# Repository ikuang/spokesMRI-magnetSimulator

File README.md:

# spokesMRI-magnetSimulator
 
 Matlab simulator for magnetic fields generated by 'spokes-and-hub' permanent magnet arrays as presented at ISMRM 2019 [1].
 
 To input magnet geometries and run simulator use:
 ```matlab 
 testMagnet.m
 ```
 
 We have provided [STL](stl) files for a 191 mT magnet constructed using 64 bar magnets (1/2" x 1/8" x 1") from [K&J Magnets](https://www.kjmagnetics.com/proddetail.asp?prod=B82X0).

 We use mechanical tilts from linear actuators to generate gradient fields within the magnet [2]. The actuators and their control boards were purchased from [Actuonix](https://www.actuonix.com/L12-P-Micro-Linear-Actuator-with-Position-Feedback-p/l12-p.htm). Instructions and [DXF](dxf) files for laser cutting acrylic are provided as well.

 We use an 8-channel STHV800 ultrasound h-bridge driver chip from [STMicroelectronics](https://www.st.com/en/switches-and-multiplexers/sthv800.html) to transmit/receive RF on a solenoid coil [3]. A Teensy 4.0 microcontroller sends RF pulses to the driver. We have provided a sample dithered RF pulse (centered at 8.18MHz with 100kHz bandwidth), Arduino code that controls the pulses and actuator movements, and Eagle PCB layouts for the ultrasound chip board. These files are found in the [signalChain](./signalChain) directory. We use a USB oscilloscope from Pico Technology ([PicoScope 5243D](https://www.picotech.com/oscilloscope/5000/flexible-resolution-oscilloscope)) to capture MR data at the Larmor frequency and perform filtering and downsampling in software. Pico Technology provides open source software development kits for Python and Matlab implementations (https://github.com/picotech). 

## References

[1] Kuang, I., Arango, N., Stockmann, J., Adalsteinsson, E., White, J. <em>Equivalent-Charge-Based Optimization of Spokes-and-Hub Magnets for Hand-Held and Classroom MR Imaging</em>. Proc. Intl. Soc. Mag. Reson. Med., 2019. 

[2] Kuang, I., Stockmann, J., Adalsteinsson, E., White, J. <em>Mechanical Tilt-Induced Gradient Fields for Low-Field Spokes-and-Hub MR Imagers</em>. Proc. Intl. Soc. Mag. Reson. Med., 2021. 

[3] Kuang, I., Arango, N., Stockmann, J., Adalsteinsson, E., White, J. <em>Bloch-Optimized Dithered-Ultrasound-Pulse RF for Low-Field Inhomogeneous Permanent Magnet MR Imagers</em>. Proc. Intl. Soc. Mag. Reson. Med., 2020. 
 
 Plotting functions use perceptually uniform colormaps from https://colorcet.com/

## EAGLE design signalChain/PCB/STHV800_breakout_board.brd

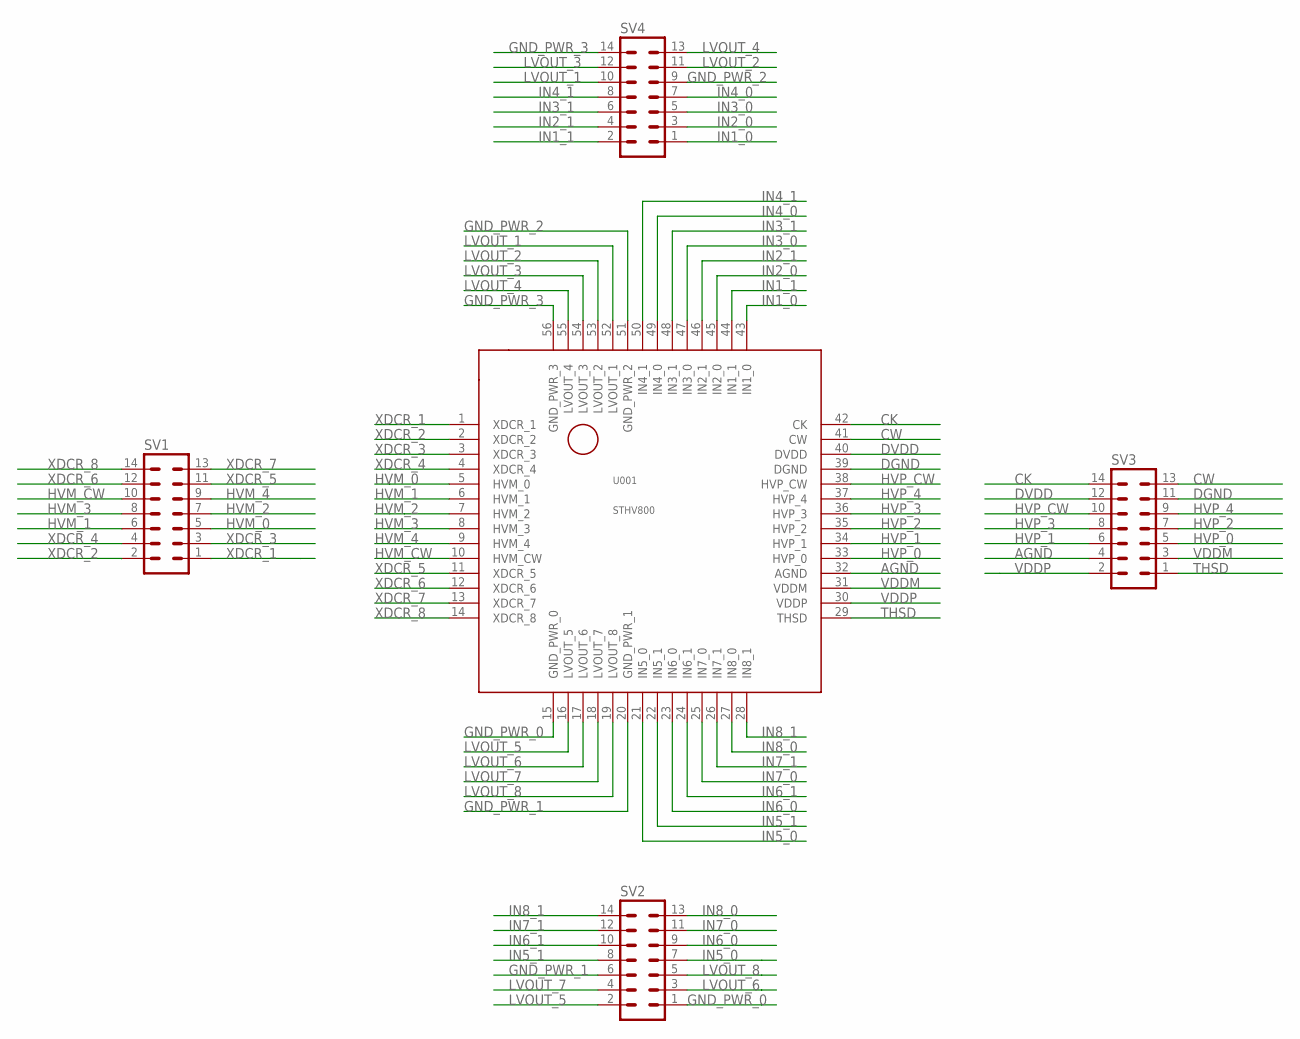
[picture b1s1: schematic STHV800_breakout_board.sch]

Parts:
SV1, SV2, SV3, SV4: MA07-2
U001: STHV800

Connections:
AGND: SV3.4, U001.32 (AGND)
CK: SV3.14, U001.42 (CK)
CW: SV3.13, U001.41 (CW)
DGND: SV3.11, U001.39 (DGND)
DVDD: SV3.12, U001.40 (DVDD)
GND_PWR_0: SV2.1, U001.15 (GND_PWR_0)
GND_PWR_1: SV2.6, U001.20 (GND_PWR_1)
GND_PWR_2: SV4.9, U001.51 (GND_PWR_2)
GND_PWR_3: SV4.14, U001.56 (GND_PWR_3)
HVM_0: SV1.5, U001.5 (HVM_0)
HVM_1: SV1.6, U001.6 (HVM_1)
HVM_2: SV1.7, U001.7 (HVM_2)
HVM_3: SV1.8, U001.8 (HVM_3)
HVM_4: SV1.9, U001.9 (HVM_4)
HVM_CW: SV1.10, U001.10 (HVM_CW)
HVP_0: SV3.5, U001.33 (HVP_0)
HVP_1: SV3.6, U001.34 (HVP_1)
HVP_2: SV3.7, U001.35 (HVP_2)
HVP_3: SV3.8, U001.36 (HVP_3)
HVP_4: SV3.9, U001.37 (HVP_4)
HVP_CW: SV3.10, U001.38 (HVP_CW)
IN1_0: SV4.1, U001.43 (IN1_0)
IN1_1: SV4.2, U001.44 (IN1_1)
IN2_0: SV4.3, U001.45 (IN2_0)
IN2_1: SV4.4, U001.46 (IN2_1)
IN3_0: SV4.5, U001.47 (IN3_0)
IN3_1: SV4.6, U001.48 (IN3_1)
IN4_0: SV4.7, U001.49 (IN4_0)
IN4_1: SV4.8, U001.50 (IN4_1)
IN5_0: SV2.7, U001.21 (IN5_0)
IN5_1: SV2.8, U001.22 (IN5_1)
IN6_0: SV2.9, U001.23 (IN6_0)
IN6_1: SV2.10, U001.24 (IN6_1)
IN7_0: SV2.11, U001.25 (IN7_0)
IN7_1: SV2.12, U001.26 (IN7_1)
IN8_0: SV2.13, U001.27 (IN8_0)
IN8_1: SV2.14, U001.28 (IN8_1)
LVOUT_1: SV4.10, U001.52 (LVOUT_1)
LVOUT_2: SV4.11, U001.53 (LVOUT_2)
LVOUT_3: SV4.12, U001.54 (LVOUT_3)
LVOUT_4: SV4.13, U001.55 (LVOUT_4)
LVOUT_5: SV2.2, U001.16 (LVOUT_5)
LVOUT_6: SV2.3, U001.17 (LVOUT_6)
LVOUT_7: SV2.4, U001.18 (LVOUT_7)
LVOUT_8: SV2.5, U001.19 (LVOUT_8)
THSD: SV3.1, U001.29 (THSD)
VDDM: SV3.3, U001.31 (VDDM)
VDDP: SV3.2, U001.30 (VDDP)
XDCR_1: SV1.1, U001.1 (XDCR_1)
XDCR_2: SV1.2, U001.2 (XDCR_2)
XDCR_3: SV1.3, U001.3 (XDCR_3)
XDCR_4: SV1.4, U001.4 (XDCR_4)
XDCR_5: SV1.11, U001.11 (XDCR_5)
XDCR_6: SV1.12, U001.12 (XDCR_6)
XDCR_7: SV1.13, U001.13 (XDCR_7)
XDCR_8: SV1.14, U001.14 (XDCR_8)

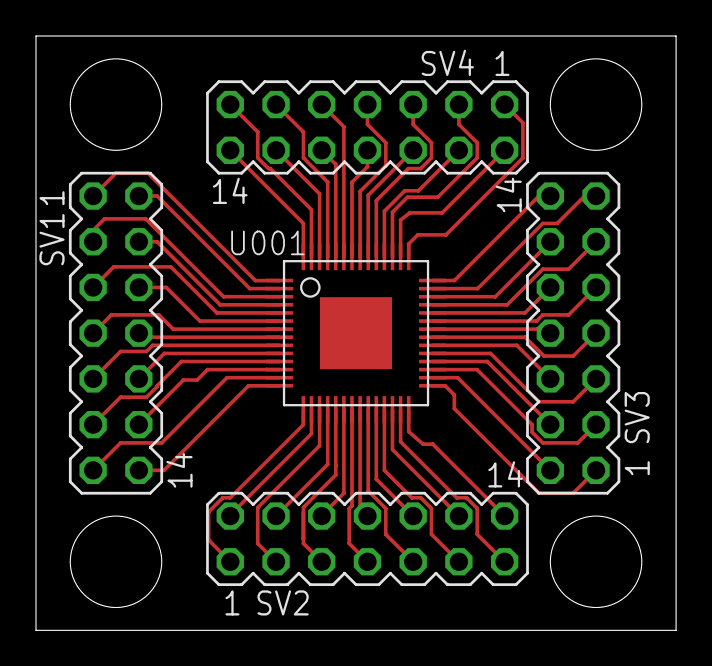
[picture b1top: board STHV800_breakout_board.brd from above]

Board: 2 copper layers, 35.6 x 33.0 mm, 5 parts (0 on the bottom side), 56 nets.

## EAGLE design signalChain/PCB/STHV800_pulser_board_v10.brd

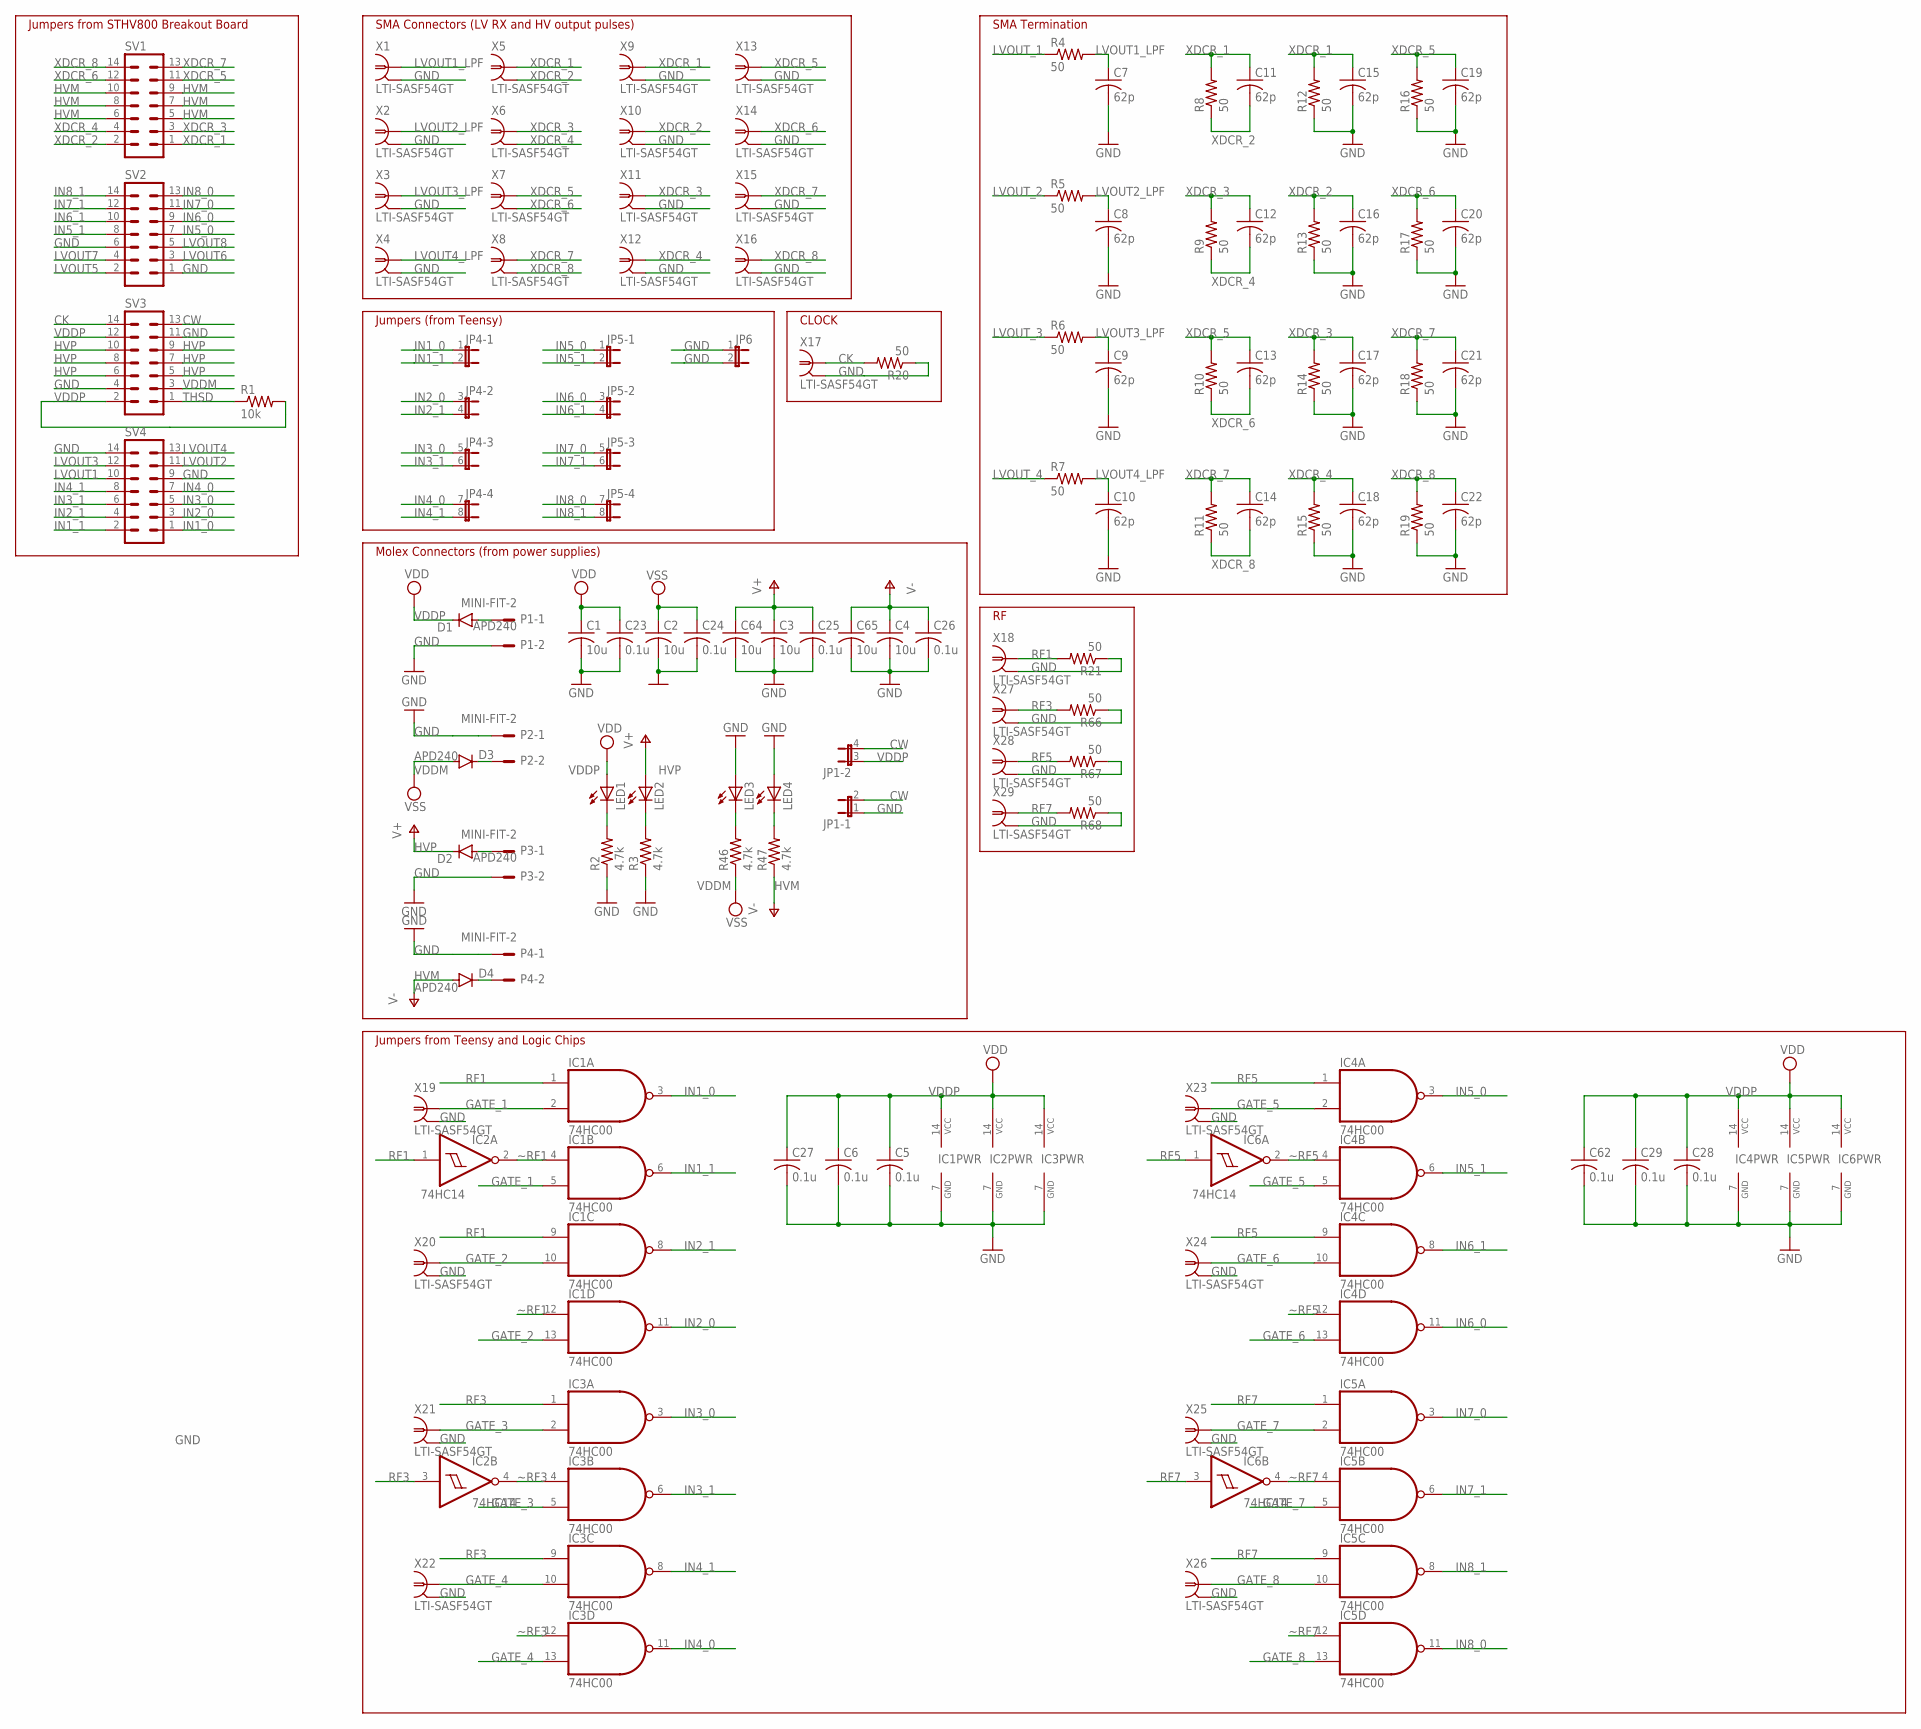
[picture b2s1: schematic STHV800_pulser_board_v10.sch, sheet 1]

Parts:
C1, C2: 10u; C1206
C3, C4, C64, C65: 10u; C1210
C5, C6, C23, C24, C25, C26, C27, C28, C29, C62: 0.1u; C0805
C7, C8, C9, C10, C11, C12, C13, C14, C15, C16, C17, C18, C19, C20, C21, C22: 62p; C0805
D1, D2, D3, D4: APD240; SOD-123_MINI-SMA
IC1, IC3, IC4, IC5: 74HC00; TSSOP14
IC2, IC6: 74HC14; TSSOP14
JP1: JP2QE; JP2Q
JP4, JP5: JP4QE; JP4Q
JP6: JP1E; JP1
LED1, LED2, LED3, LED4: LEDSMT1206; 1206
P1, P2, P3, P4: MINI-FIT-2; CON-MOLEX-MINI-FIT_39-30-?02?
R1: 10k; R0805
R2, R3, R46, R47: 4.7k; R0805
R4, R5, R6, R7, R8, R9, R10, R11, R12, R13, R14, R15, R16, R17, R18, R19: 50; R1206
R20, R21, R66, R67, R68: 50; R0805
SV1, SV2, SV3, SV4: MA07-2
X1, X2, X3, X4, X5, X6, X7, X8, X9, X10, X11, X12, X13, X14, X15, X16, X17, X18, X19, X20, X21, X22, X23, X24, X25, X26, X27, X28, X29: LTI-SASF54GT

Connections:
CK: R20.2, SV3.14, X17.1
CW: JP1.2, JP1.4 (2), SV3.13
GATE_1: IC1.2 (I1), IC1.5 (I1), X19.1
GATE_2: IC1.10 (I1), IC1.13 (I1), X20.1
GATE_3: IC3.2 (I1), IC3.5 (I1), X21.1
GATE_4: IC3.10 (I1), IC3.13 (I1), X22.1
GATE_5: IC4.2 (I1), IC4.5 (I1), X23.1
GATE_6: IC4.10 (I1), IC4.13 (I1), X24.1
GATE_7: IC5.2 (I1), IC5.5 (I1), X25.1
GATE_8: IC5.10 (I1), IC5.13 (I1), X26.1
GND: C1.2, C2.2, C3.2, C4.2, C5.2, C6.2, C7.2, C8.2, C9.2, C10.2, C15.2, C16.2, C17.2, C18.2, C19.2, C20.2, C21.2, C22.2, C23.2, C24.2, C25.2, C26.2, C27.2, C28.2, C29.2, C62.2, C64.2, C65.2, IC1.7 (GND), IC2.7 (GND), IC3.7 (GND), IC4.7 (GND), IC5.7 (GND), IC6.7 (GND), JP1.1, JP6.1, JP6.2, LED3.A, LED4.A, P1.2, P2.1, P3.2, P4.1, R2.1, R3.1, R12.1, R13.1, R14.1, R15.1, R16.1, R17.1, R18.1, R19.1, R20.1, R21.1, R66.1, R67.1, R68.1, SV2.1, SV2.6, SV3.4, SV3.11, SV4.9, SV4.14, X1.2, X1.3 (2), X1.4 (2), X1.5 (2), X2.2, X2.3 (2), X2.4 (2), X2.5 (2), X3.2, X3.3 (2), X3.4 (2), X3.5 (2), X4.2, X4.3 (2), X4.4 (2), X4.5 (2), X9.2, X9.3 (2), X9.4 (2), X9.5 (2), X10.2, X10.3 (2), X10.4 (2), X10.5 (2), X11.2, X11.3 (2), X11.4 (2), X11.5 (2), X12.2, X12.3 (2), X12.4 (2), X12.5 (2), X13.2, X13.3 (2), X13.4 (2), X13.5 (2), X14.2, X14.3 (2), X14.4 (2), X14.5 (2), X15.2, X15.3 (2), X15.4 (2), X15.5 (2), X16.2, X16.3 (2), X16.4 (2), X16.5 (2), X17.2, X17.3 (2), X17.4 (2), X17.5 (2), X18.2, X18.3 (2), X18.4 (2), X18.5 (2), X19.2, X19.3 (2), X19.4 (2), X19.5 (2), X20.2, X20.3 (2), X20.4 (2), X20.5 (2), X21.2, X21.3 (2), X21.4 (2), X21.5 (2), X22.2, X22.3 (2), X22.4 (2), X22.5 (2), X23.2, X23.3 (2), X23.4 (2), X23.5 (2), X24.2, X24.3 (2), X24.4 (2), X24.5 (2), X25.2, X25.3 (2), X25.4 (2), X25.5 (2), X26.2, X26.3 (2), X26.4 (2), X26.5 (2), X27.2, X27.3 (2), X27.4 (2), X27.5 (2), X28.2, X28.3 (2), X28.4 (2), X28.5 (2), X29.2, X29.3 (2), X29.4 (2), X29.5 (2); also elsewhere on the board
HVM: C4.1, C26.1, C65.1, D4.A, R47.1, SV1.5, SV1.6, SV1.7, SV1.8, SV1.9, SV1.10
HVP: C3.1, C25.1, C64.1, D2.C, LED2.A, SV3.5, SV3.6, SV3.7, SV3.8, SV3.9, SV3.10
HVP_1: D2.A, P3.1
IN1_0: IC1.3 (O), JP4.1, SV4.1
IN1_1: IC1.6 (O), JP4.2, SV4.2
IN2_0: IC1.11 (O), JP4.3 (1), SV4.3
IN2_1: IC1.8 (O), JP4.4 (2), SV4.4
IN3_0: IC3.3 (O), JP4.5 (1), SV4.5
IN3_1: IC3.6 (O), JP4.6 (2), SV4.6
IN4_0: IC3.11 (O), JP4.7 (1), SV4.7
IN4_1: IC3.8 (O), JP4.8 (2), SV4.8
IN5_0: IC4.3 (O), JP5.1, SV2.7
IN5_1: IC4.6 (O), JP5.2, SV2.8
IN6_0: IC4.11 (O), JP5.3 (1), SV2.9
IN6_1: IC4.8 (O), JP5.4 (2), SV2.10
IN7_0: IC5.3 (O), JP5.5 (1), SV2.11
IN7_1: IC5.6 (O), JP5.6 (2), SV2.12
IN8_0: IC5.11 (O), JP5.7 (1), SV2.13
IN8_1: IC5.8 (O), JP5.8 (2), SV2.14
LVOUT1: SV4.10; also elsewhere on the board
LVOUT1_LPF: C7.1, R4.2, X1.1
LVOUT2: SV4.11; also elsewhere on the board
LVOUT2_LPF: C8.1, R5.2, X2.1
LVOUT3: SV4.12; also elsewhere on the board
LVOUT3_LPF: C9.1, R6.2, X3.1
LVOUT4: SV4.13; also elsewhere on the board
LVOUT4_LPF: C10.1, R7.2, X4.1
LVOUT5: SV2.2; also elsewhere on the board
LVOUT6: SV2.3; also elsewhere on the board
LVOUT7: SV2.4; also elsewhere on the board
LVOUT8: SV2.5; also elsewhere on the board
LVOUT_1: R4.1; also elsewhere on the board
LVOUT_2: R5.1; also elsewhere on the board
LVOUT_3: R6.1; also elsewhere on the board
LVOUT_4: R7.1; also elsewhere on the board
unnamed: LED1.C, R2.2
unnamed: LED2.C, R3.2
unnamed: LED3.C, R46.2
unnamed: LED4.C, R47.2
unnamed: D3.C, P2.2
unnamed: D4.C, P4.2
RF1: IC1.1 (I0), IC1.9 (I0), IC2.1 (I), R21.2, X18.1
RF3: IC2.3 (I), IC3.1 (I0), IC3.9 (I0), R66.2, X27.1
RF5: IC4.1 (I0), IC4.9 (I0), IC6.1 (I), R67.2, X28.1
RF7: IC5.1 (I0), IC5.9 (I0), IC6.3 (I), R68.2, X29.1
THSD: R1.1, SV3.1
VDDM: C2.1, C24.1, D3.A, R46.1, SV3.3; also elsewhere on the board
VDDP: C1.1, C5.1, C6.1, C23.1, C27.1, C28.1, C29.1, C62.1, D1.C, IC1.14 (VCC), IC2.14 (VCC), IC3.14 (VCC), IC4.14 (VCC), IC5.14 (VCC), IC6.14 (VCC), JP1.3 (1), LED1.A, R1.2, SV3.2, SV3.12; also elsewhere on the board
VDDP_1: D1.A, P1.1
XDCR_1: C11.1, C15.1, R8.2, R12.2, SV1.1, X5.1, X9.1
XDCR_2: C11.2, C16.1, R8.1, R13.2, SV1.2, X5.2, X5.3 (2), X5.4 (2), X5.5 (2), X10.1
XDCR_3: C12.1, C17.1, R9.2, R14.2, SV1.3, X6.1, X11.1
XDCR_4: C12.2, C18.1, R9.1, R15.2, SV1.4, X6.2, X6.3 (2), X6.4 (2), X6.5 (2), X12.1
XDCR_5: C13.1, C19.1, R10.2, R16.2, SV1.11, X7.1, X13.1
XDCR_6: C13.2, C20.1, R10.1, R17.2, SV1.12, X7.2, X7.3 (2), X7.4 (2), X7.5 (2), X14.1
XDCR_7: C14.1, C21.1, R11.2, R18.2, SV1.13, X8.1, X15.1
XDCR_8: C14.2, C22.1, R11.1, R19.2, SV1.14, X8.2, X8.3 (2), X8.4 (2), X8.5 (2), X16.1
~RF1: IC1.4 (I0), IC1.12 (I0), IC2.2 (O)
~RF3: IC2.4 (O), IC3.4 (I0), IC3.12 (I0)
~RF5: IC4.4 (I0), IC4.12 (I0), IC6.2 (O)
~RF7: IC5.4 (I0), IC5.12 (I0), IC6.4 (O)

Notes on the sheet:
SMA Connectors (LV RX and HV output pulses)
Jumpers (from Teensy)
Molex Connectors (from power supplies)
CLOCK
Jumpers from Teensy and Logic Chips
Jumpers from STHV800 Breakout Board
SMA Termination

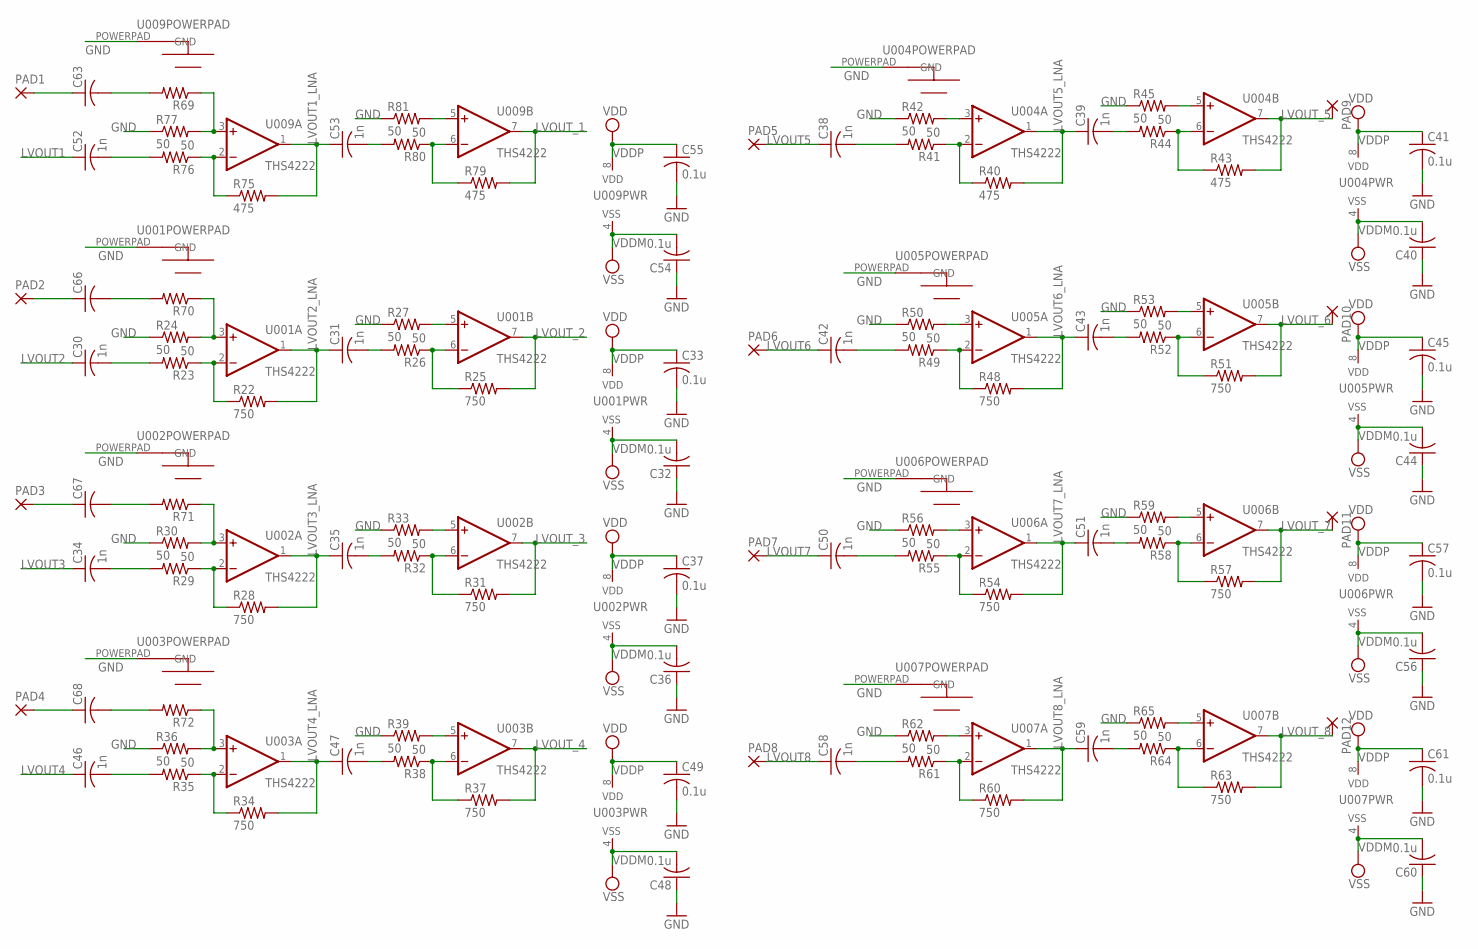
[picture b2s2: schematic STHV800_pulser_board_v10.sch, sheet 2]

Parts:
C30, C31, C34, C35, C38, C39, C42, C43, C46, C47, C50, C51, C52, C53, C58, C59: 1n; C0805
C32, C33, C36, C37, C40, C41, C44, C45, C48, C49, C54, C55, C56, C57, C60, C61: 0.1u; C0805
C63, C66, C67, C68: C-USC0805; C0805
PAD1, PAD2, PAD3, PAD4, PAD5, PAD6, PAD7, PAD8, PAD9, PAD10, PAD11, PAD12: 1,6/0,8
R22, R25, R28, R31, R34, R37, R48, R51, R54, R57, R60, R63: 750; R0805
R23, R24, R26, R27, R29, R30, R32, R33, R35, R36, R38, R39, R41, R42, R44, R45, R49, R50, R52, R53, R55, R56, R58, R59, R61, R62, R64, R65, R76, R77, R80, R81: 50; R0805
R40, R43, R75, R79: 475; R0805
R69, R70, R71, R72: R-US_R0805; R0805
U001, U002, U003, U004, U005, U006, U007, U009: THS4222; SSOP08-POWERPAD

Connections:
GND: C32.1, C33.2, C36.1, C37.2, C40.1, C41.2, C44.1, C45.2, C48.1, C49.2, C54.1, C55.2, C56.1, C57.2, C60.1, C61.2, R24.1, R27.1, R30.1, R33.1, R36.1, R39.1, R42.1, R45.1, R50.1, R53.1, R56.1, R59.1, R62.1, R65.1, R77.1, R81.1, U001.POWERPAD (GND), U002.POWERPAD (GND), U003.POWERPAD (GND), U004.POWERPAD (GND), U005.POWERPAD (GND), U006.POWERPAD (GND), U007.POWERPAD (GND), U009.POWERPAD (GND); also elsewhere on the board
LVOUT1: C52.1; also elsewhere on the board
LVOUT1_LNA: C53.1, R75.2, U009.1 (OUT)
LVOUT2: C30.1; also elsewhere on the board
LVOUT2_LNA: C31.1, R22.2, U001.1 (OUT)
LVOUT3: C34.1; also elsewhere on the board
LVOUT3_LNA: C35.1, R28.2, U002.1 (OUT)
LVOUT4: C46.1; also elsewhere on the board
LVOUT4_LNA: C47.1, R34.2, U003.1 (OUT)
LVOUT5: C38.1, PAD5.1; also elsewhere on the board
LVOUT5_LNA: C39.1, R40.2, U004.1 (OUT)
LVOUT6: C42.1, PAD6.1; also elsewhere on the board
LVOUT6_LNA: C43.1, R48.2, U005.1 (OUT)
LVOUT7: C50.1, PAD7.1; also elsewhere on the board
LVOUT7_LNA: C51.1, R54.2, U006.1 (OUT)
LVOUT8: C58.1, PAD8.1; also elsewhere on the board
LVOUT8_LNA: C59.1, R60.2, U007.1 (OUT)
LVOUT_1: R79.2, U009.7 (OUT); also elsewhere on the board
LVOUT_2: R25.2, U001.7 (OUT); also elsewhere on the board
LVOUT_3: R31.2, U002.7 (OUT); also elsewhere on the board
LVOUT_4: R37.2, U003.7 (OUT); also elsewhere on the board
LVOUT_5: PAD9.1, R43.2, U004.7 (OUT)
LVOUT_6: PAD10.1, R51.2, U005.7 (OUT)
LVOUT_7: PAD11.1, R57.2, U006.7 (OUT)
LVOUT_8: PAD12.1, R63.2, U007.7 (OUT)
unnamed: R25.1, R26.1, U001.6 (-IN)
unnamed: R24.2, R70.1, U001.3 (+IN)
unnamed: R22.1, R23.1, U001.2 (-IN)
unnamed: C30.2, R23.2
unnamed: C31.2, R26.2
unnamed: R27.2, U001.5 (+IN)
unnamed: R31.1, R32.1, U002.6 (-IN)
unnamed: R30.2, R71.1, U002.3 (+IN)
unnamed: R43.1, R44.1, U004.6 (-IN)
unnamed: R42.2, U004.3 (+IN)
unnamed: R40.1, R41.1, U004.2 (-IN)
unnamed: C38.2, R41.2
unnamed: C39.2, R44.2
unnamed: R45.2, U004.5 (+IN)
unnamed: R51.1, R52.1, U005.6 (-IN)
unnamed: R28.1, R29.1, U002.2 (-IN)
unnamed: C34.2, R29.2
unnamed: C35.2, R32.2
unnamed: R33.2, U002.5 (+IN)
unnamed: R37.1, R38.1, U003.6 (-IN)
unnamed: R36.2, R72.1, U003.3 (+IN)
unnamed: R34.1, R35.1, U003.2 (-IN)
unnamed: C46.2, R35.2
unnamed: C47.2, R38.2
unnamed: R39.2, U003.5 (+IN)
unnamed: R50.2, U005.3 (+IN)
unnamed: R48.1, R49.1, U005.2 (-IN)
unnamed: C42.2, R49.2
unnamed: C43.2, R52.2
unnamed: R53.2, U005.5 (+IN)
unnamed: R57.1, R58.1, U006.6 (-IN)
unnamed: R56.2, U006.3 (+IN)
unnamed: R54.1, R55.1, U006.2 (-IN)
unnamed: C50.2, R55.2
unnamed: C51.2, R58.2
unnamed: R59.2, U006.5 (+IN)
unnamed: R63.1, R64.1, U007.6 (-IN)
unnamed: R62.2, U007.3 (+IN)
unnamed: R60.1, R61.1, U007.2 (-IN)
unnamed: C58.2, R61.2
unnamed: C59.2, R64.2
unnamed: R65.2, U007.5 (+IN)
unnamed: C63.2, R69.2
unnamed: C67.2, R71.2
unnamed: C66.2, R70.2
unnamed: C68.2, R72.2
unnamed: R79.1, R80.1, U009.6 (-IN)
unnamed: R69.1, R77.2, U009.3 (+IN)
unnamed: R75.1, R76.1, U009.2 (-IN)
unnamed: C52.2, R76.2
unnamed: C53.2, R80.2
unnamed: R81.2, U009.5 (+IN)
TEST_VIA_1: C63.1, PAD1.1
TEST_VIA_2: C66.1, PAD2.1
TEST_VIA_3: C67.1, PAD3.1
TEST_VIA_4: C68.1, PAD4.1
VDDM: C32.2, C36.2, C40.2, C44.2, C48.2, C54.2, C56.2, C60.2, U001.4 (VSS), U002.4 (VSS), U003.4 (VSS), U004.4 (VSS), U005.4 (VSS), U006.4 (VSS), U007.4 (VSS), U009.4 (VSS); also elsewhere on the board
VDDP: C33.1, C37.1, C41.1, C45.1, C49.1, C55.1, C57.1, C61.1, U001.8 (VDD), U002.8 (VDD), U003.8 (VDD), U004.8 (VDD), U005.8 (VDD), U006.8 (VDD), U007.8 (VDD), U009.8 (VDD); also elsewhere on the board

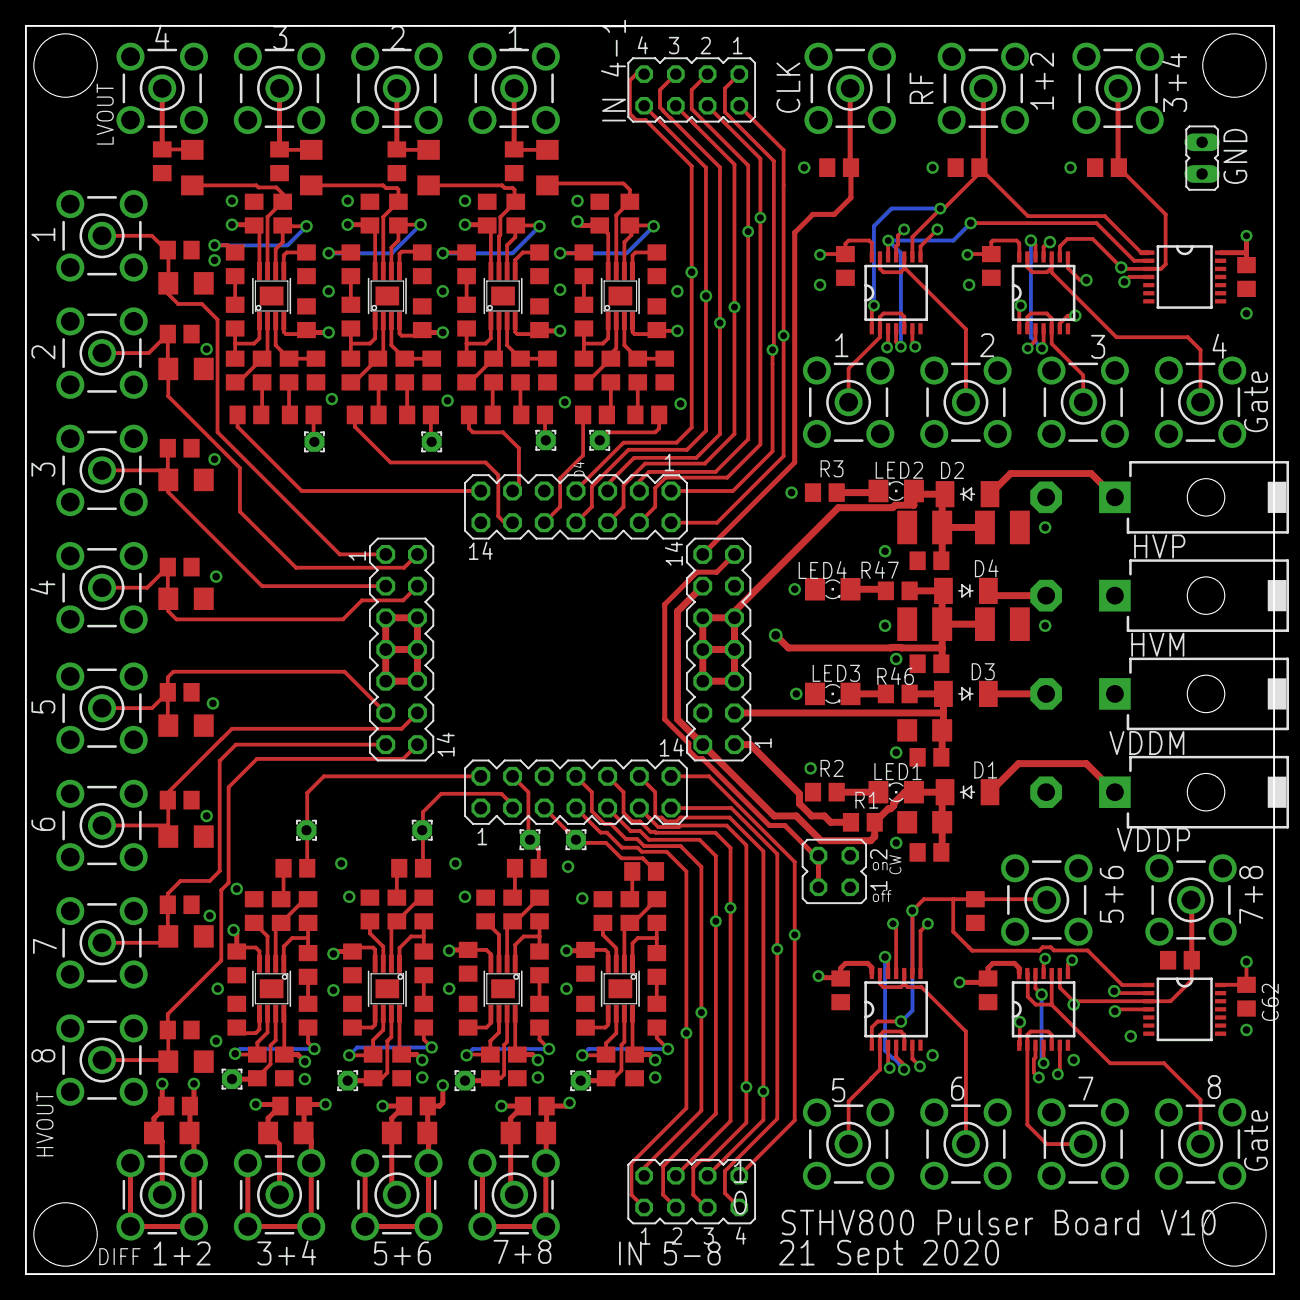
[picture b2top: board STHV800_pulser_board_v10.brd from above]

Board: 4 copper layers, 100.0 x 100.0 mm, 221 parts (0 on the bottom side), 140 nets.

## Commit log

2021-09-01 initial code commit
2021-09-01 magnet picture
2021-09-01 uploaded simulated field pic
2021-09-01 added 3d print STLs
2021-09-08 added dxf files for laser cutting
2021-09-08 teensy code for RF and linear actuator control
2021-09-08 pcb files for ultrasound signal chain
2021-09-08 code for generating RF and controlling linear actuators
2021-09-22 sthv breakout board pcb files
2021-09-22 signal chain PCB gerber files
